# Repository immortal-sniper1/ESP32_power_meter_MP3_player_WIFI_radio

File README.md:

# PCB_test_project_01
 First ESP32 pcb project, it will have power meters( 24V 3A, 5V 0.5A, and self consumption), uSD card, WIFI/BT and the ability to play back MP3/audio file.     
 Also it will feature a power usage meter. It can also be powered from a 18650 Li ion cell, if the USB is alsoo pluged in the cell will start chargeing.
 The chargeing current is limited by the chargeing IC useing a potenciometer as the input. If the red LED is on then the cell is cahrgeing and if the green
 LED is on then the cell is fully charged.
 NOTE: the voltage levels are set by the ICs and it is : 4.2V as charged state and 3V as discharged.
 If the cel voltage reaches 3V or lower then a circuit will activate and disconect the cell from the system so that it will not overdischarge.
 
 V1 is made with ESP32-MINI and that is super hard to hand assemble so V2+ wil use the VROOM

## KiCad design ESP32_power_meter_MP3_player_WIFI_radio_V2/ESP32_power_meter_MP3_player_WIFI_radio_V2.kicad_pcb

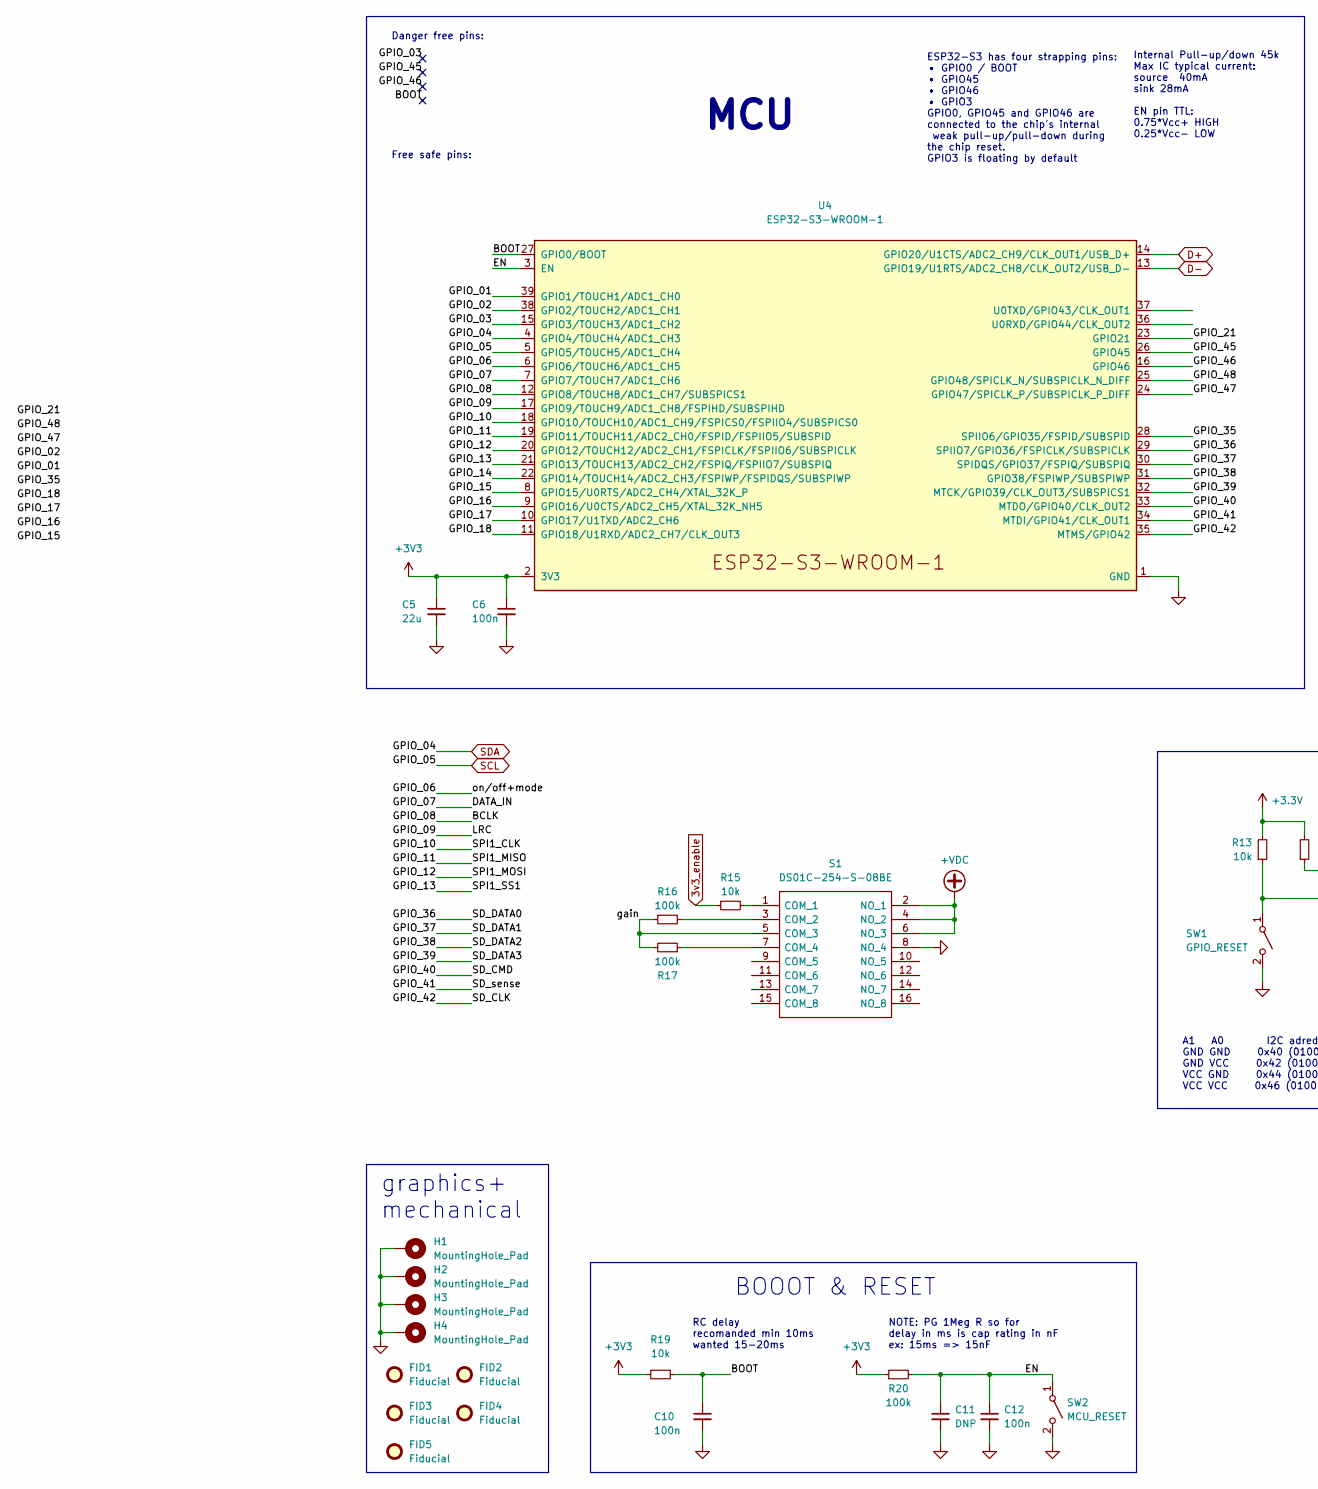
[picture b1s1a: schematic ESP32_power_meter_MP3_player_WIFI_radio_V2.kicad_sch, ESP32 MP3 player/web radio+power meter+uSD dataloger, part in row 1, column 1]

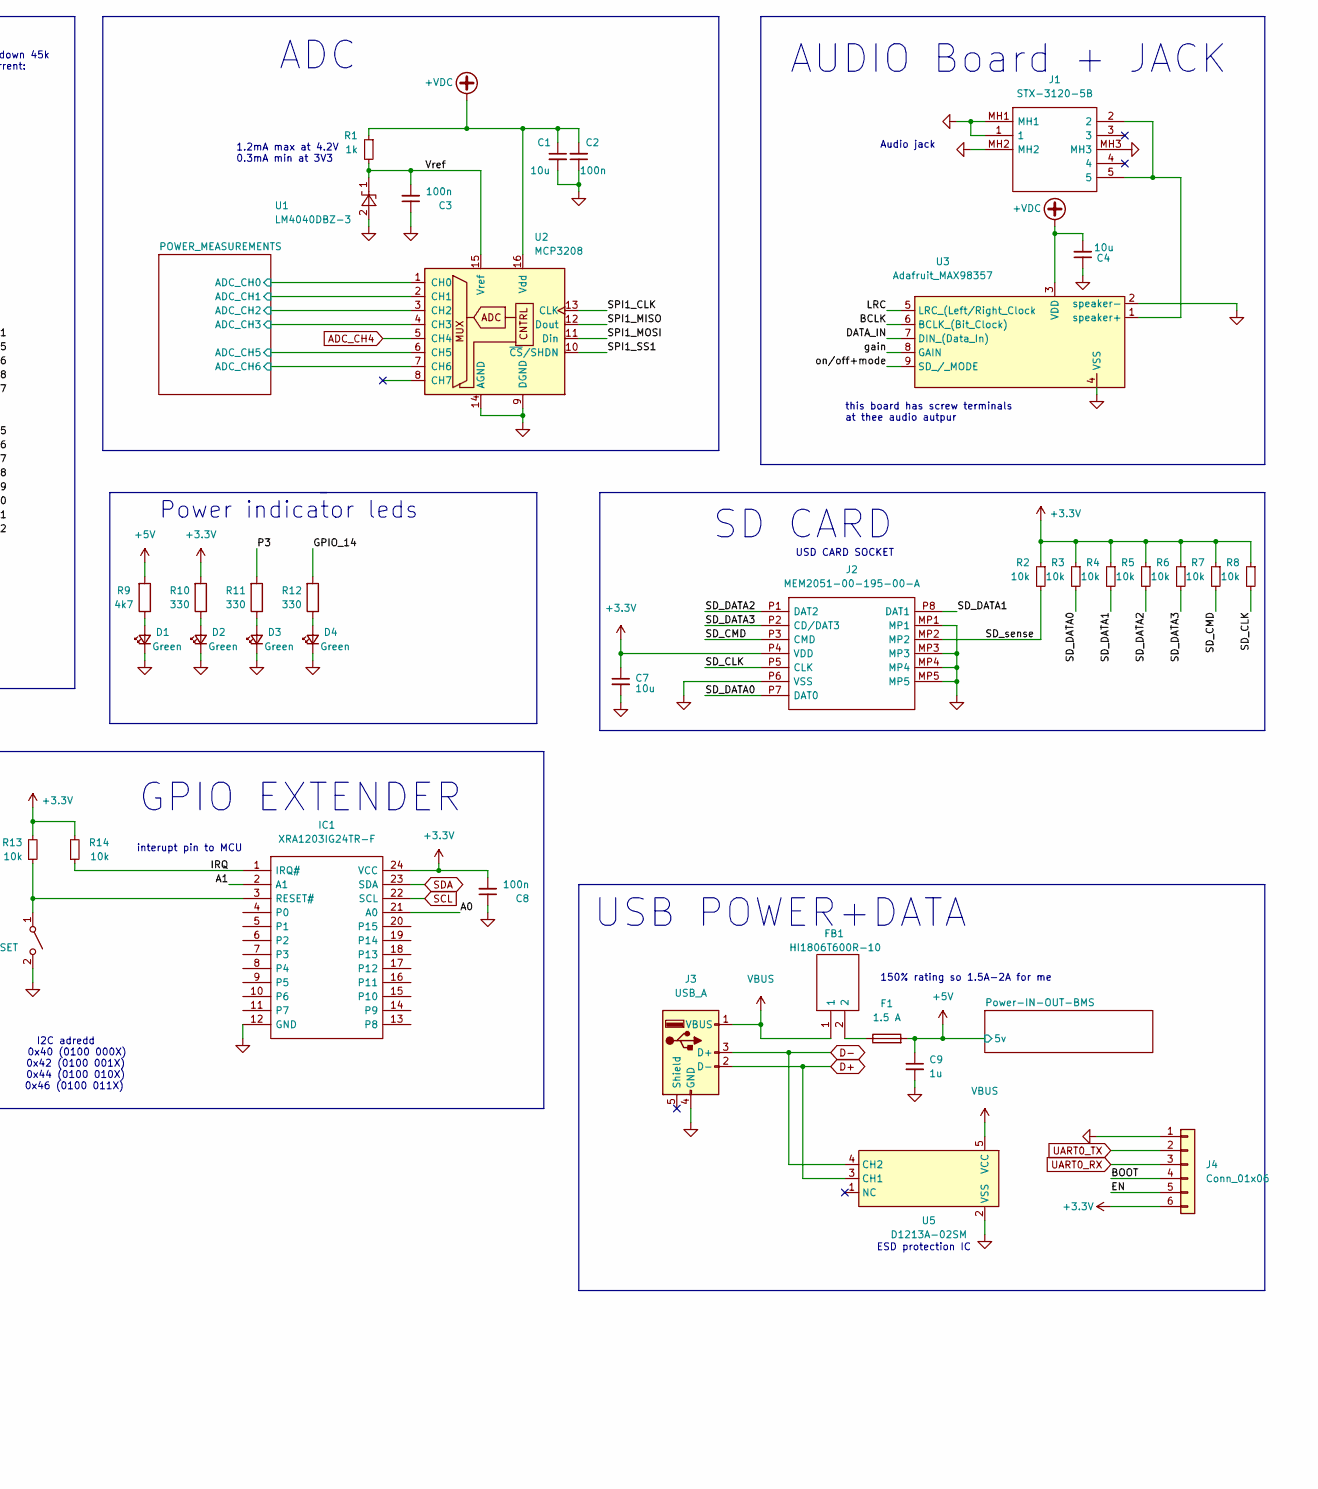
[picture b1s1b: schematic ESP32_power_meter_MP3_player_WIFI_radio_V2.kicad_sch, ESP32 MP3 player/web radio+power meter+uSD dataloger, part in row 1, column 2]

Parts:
C1, C4, C7: 10u; C_0805_2012Metric
C2, C3, C6, C8, C10, C12: 100n; C_0603_1608Metric_Pad1.08x0.95mm_HandSolder
C5: 22u; C_0805_2012Metric_Pad1.18x1.45mm_HandSolder
C9: 1u; C_0603_1608Metric_Pad1.08x0.95mm_HandSolder
C11: DNP; C_0603_1608Metric_Pad1.08x0.95mm_HandSolder
D1, D2, D3, D4: Green; LED_0603_1608Metric_Pad1.05x0.95mm_HandSolder
F1: 1.5 A; Fuse_1812_4532Metric
FB1: HI1806T600R-10; BEADC4516X185N; Mouser Part Number 875-HI1806T600R-10
FID1: Fiducial; Fiducial_0.5mm_Mask1mm
FID2: Fiducial; KiCad-Logo2_6mm_SilkScreen
FID3: Fiducial; Polarity_Center_Positive_6mm_SilkScreen
FID4: Fiducial; WEEE-Logo_5.6x8mm_SilkScreen
FID5: Fiducial; OSHW-Logo_5.7x6mm_SilkScreen
H1, H2, H3, H4: MountingHole_Pad; MountingHole_3.2mm_M3
IC1: XRA1203IG24TR-F; SOP65P640X120-24N; Mouser Part Number 701-XRA1203IG24TR-F
J1: STX-3120-5B; STX31205B; Mouser Part Number 806-STX-3120-5B
J2: MEM2051-00-195-00-A; MEM20510019500A; Mouser Part Number 640-MEM20510019500A
J3: USB_A; USB_A_Molex_67643_Horizontal
J4: Conn_01x06; PinHeader_1x06_P2.54mm_Vertical
R1: 1k; R_0603_1608Metric_Pad0.98x0.95mm_HandSolder
R2, R3, R4, R5, R6, R7, R8, R13, R14, R15, R19: 10k; R_0603_1608Metric_Pad0.98x0.95mm_HandSolder
R9: 4k7; R_0603_1608Metric_Pad0.98x0.95mm_HandSolder
R10, R11, R12: 330; R_0603_1608Metric_Pad0.98x0.95mm_HandSolder
R16, R17, R20: 100k; R_0603_1608Metric_Pad0.98x0.95mm_HandSolder
S1: DS01C-254-S-08BE; DS01C254S08BE; Mouser Part Number 490-DS01C-254-S-08BE
SW1: GPIO_RESET; PTS526SK15SMTR2LFS
SW2: MCU_RESET; PTS526SK15SMTR2LFS
U1: LM4040DBZ-3; SOT-23
U2: MCP3208; SOIC-16_3.9x9.9mm_P1.27mm
U3: Adafruit_MAX98357; Adafruit MAX98357 I2S Class-D Mono
U4: ESP32-S3-WROOM-1
U5: D1213A-02SM; SOT-23-5_HandSoldering

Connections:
3v3_enable: R15.1; also elsewhere on the board
+3.3V: C7.1, C8.2, IC1.24 (VCC), J2.P4 (VDD), J4.6, R2.1, R3.1, R4.1, R5.1, R6.1, R7.1, R8.1, R10.2, R13.2, R14.2; also elsewhere on the board
+3V3: C5.1, C6.1, R19.2, R20.1, U4.2 (3V3); also elsewhere on the board
+5V: C9.1, F1.2, R9.2; also elsewhere on the board
+VDC: C1.1, C2.2, C4.2, R1.1, S1.2 (NO_1), S1.4 (NO_2), S1.6 (NO_3), U2.16 (Vdd), U3.3 (VDD); also elsewhere on the board
/A0: IC1.21 (A0)
/A1: IC1.2 (A1)
/BCLK: U3.6 (BCLK_(Bit_Clock)), U4.12 (GPIO8/TOUCH8/ADC1_CH7/SUBSPICS1)
/BOOT: C10.1, J4.4, R19.1, U4.27 (GPIO0/BOOT)
/DATA_IN: U3.7 (DIN_(Data_In)), U4.7 (GPIO7/TOUCH7/ADC1_CH6)
/EN: C11.1, C12.1, J4.5, R20.2, SW2.1 (A), U4.3 (EN)
/GPIO_01: U4.39 (GPIO1/TOUCH1/ADC1_CH0)
/GPIO_02: U4.38 (GPIO2/TOUCH2/ADC1_CH1)
/GPIO_03: U4.15 (GPIO3/TOUCH3/ADC1_CH2)
/GPIO_06: U3.9 (SD_/_MODE), U4.6 (GPIO6/TOUCH6/ADC1_CH5)
/GPIO_09: U3.5 (LRC_(Left/Right_Clock), U4.17 (GPIO9/TOUCH9/ADC1_CH8/FSPIHD/SUBSPIHD)
/GPIO_10: U2.13 (CLK), U4.18 (GPIO10/TOUCH10/ADC1_CH9/FSPICS0/FSPIIO4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)
/GPIO_11: U2.12 (Dout), U4.19 (GPIO11/TOUCH11/ADC2_CH0/FSPID/FSPIIO5/S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)
/GPIO_12: U2.11 (Din), U4.20 (GPIO12/TOUCH12/ADC2_CH1/FSPICLK/FSPIIO6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)
/GPIO_13: U2.10 (~CS/SHDN), U4.21 (GPIO13/TOUCH13/ADC2_CH2/FSPIQ/FSPIIO7/S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)
/GPIO_14: R12.2, U4.22 (GPIO14/TOUCH14/ADC2_CH3/FSPIWP/FSPIDQS/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)
/GPIO_15: U4.8 (GPIO15/U0RTS/ADC2_CH4/XTAL_32K_P)
/GPIO_16: U4.9 (GPIO16/U0CTS/ADC2_CH5/XTAL_32K_NH5)
/GPIO_17: U4.10 (GPIO17/U1TXD/ADC2_CH6)
/GPIO_18: U4.11 (GPIO18/U1RXD/ADC2_CH7/CLK_OUT3)
/GPIO_21: U4.23 (GPIO21)
/GPIO_35: U4.28 (SPIIO6/GPIO35/FSPID/SUBSPID)
/GPIO_36: J2.P7 (DAT0), R3.2, U4.29 (SPIIO7/GPIO36/FSPICLK/SUBSPICLK)
/GPIO_37: J2.P8 (DAT1), R4.2, U4.30 (SPIDQS/GPIO37/FSPIQ/SUBSPIQ)
/GPIO_38: J2.P1 (DAT2), R5.2, U4.31 (GPIO38/FSPIWP/SUBSPIWP)
/GPIO_39: J2.P2 (CD/DAT3), R6.2, U4.32 (MTCK/GPIO39/CLK_OUT3/SUBSPICS1)
/GPIO_40: J2.P3 (CMD), R7.2, U4.33 (MTDO/GPIO40/CLK_OUT2)
/GPIO_41: J2.MP2, R2.2, U4.34 (MTDI/GPIO41/CLK_OUT1)
/GPIO_42: J2.P5 (CLK), R8.2, U4.35 (MTMS/GPIO42)
/GPIO_45: U4.26 (GPIO45)
/GPIO_46: U4.16 (GPIO46)
/GPIO_47: U4.24 (GPIO47/SPICLK_P/SUBSPICLK_P_DIFF)
/GPIO_48: U4.25 (GPIO48/SPICLK_N/SUBSPICLK_N_DIFF)
/IRQ: IC1.1 (IRQ#), R14.1
/P3: R11.2
/POWER_MEASUREMENTS/ADC_CH0: U2.1 (CH0); also elsewhere on the board
/POWER_MEASUREMENTS/ADC_CH1: U2.2 (CH1); also elsewhere on the board
/POWER_MEASUREMENTS/ADC_CH2: U2.3 (CH2); also elsewhere on the board
/POWER_MEASUREMENTS/ADC_CH3: U2.4 (CH3); also elsewhere on the board
/POWER_MEASUREMENTS/ADC_CH5: U2.6 (CH5); also elsewhere on the board
/POWER_MEASUREMENTS/ADC_CH6: U2.7 (CH6); also elsewhere on the board
/Vref: C3.2, R1.2, U1.1 (K), U2.15 (Vref)
/gain: R16.1, R17.2, S1.5 (COM_3), U3.8 (GAIN)
ADC_CH4: U2.5 (CH4)
D+: J3.2 (D-), U4.14 (GPIO20/U1CTS/ADC2_CH9/CLK_OUT1/USB_D+), U5.3 (CH1)
D-: J3.3 (D+), U4.13 (GPIO19/U1RTS/ADC2_CH8/CLK_OUT2/USB_D-), U5.4 (CH2)
GND: C1.2, C2.1, C3.1, C4.1, C5.2, C6.2, C7.2, C8.1, C9.2, C10.2, C11.2, C12.2, D1.1 (K), D2.1 (K), D3.1 (K), D4.1 (K), H1.1, H2.1, H3.1, H4.1, IC1.12 (GND), J1.1, J1.MH1, J1.MH2, J1.MH3, J2.MP1, J2.MP3, J2.MP4, J2.MP5, J2.P6 (VSS), J3.4 (GND), J4.1, S1.8 (NO_4), SW1.2 (B), SW2.2 (B), U1.2 (A), U2.9 (DGND), U2.14 (AGND), U3.2 (speaker-), U3.4 (VSS), U4.1 (GND), U4.40 (GND), U4.41 (GND), U5.2 (VSS); also elsewhere on the board
unnamed: D1.2 (A), R9.1
unnamed: D2.2 (A), R10.1
unnamed: D3.2 (A), R11.1
unnamed: D4.2 (A), R12.1
unnamed: F1.1, FB1.2
unnamed: IC1.3 (RESET#), R13.1, SW1.1 (A)
unnamed: J1.2, J1.5, U3.1 (speaker+)
unnamed: R15.2, S1.1 (COM_1)
unnamed: R16.2, S1.3 (COM_2)
unnamed: R17.1, S1.7 (COM_4)
SCL: IC1.22 (SCL), U4.5 (GPIO5/TOUCH5/ADC1_CH4)
SDA: IC1.23 (SDA), U4.4 (GPIO4/TOUCH4/ADC1_CH3)
UART0_RX: J4.3
UART0_TX: J4.2
VBUS: FB1.1, J3.1 (VBUS), U5.5 (VCC)

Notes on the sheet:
AUDIO Board + JACK
interupt pin to MCU
USD CARD SOCKET
RC delay recomanded min 10ms wanted 15-20ms
Free safe pins:
Power indicator leds
NOTE: PG 1Meg R so for delay in ms is cap rating in nF ex: 15ms => 15nF
150% rating so 1.5A-2A for me
MCU
ESD protection IC
ESP32-S3 has four strapping pins: • GPIO0 / BOOT • GPIO45 • GPIO46 • GPIO3 GPIO0, GPIO45 and GPIO46 are connected to the chip's internal weak pull-up/pull-down during the chip reset. GPIO3 is floating by default
Internal Pull-up/down 45k Max IC typical current: source 40mA sink 28mA EN pin TTL: 0.75*Vcc+ HIGH 0.25*Vcc- LOW
A1 A0 I2C adredd GND GND 0x40 (0100 000X) GND VCC 0x42 (0100 001X) VCC GND 0x44 (0100 010X) VCC VCC 0x46 (0100 011X)
GPIO EXTENDER
SD CARD
Danger free pins:
USB POWER+DATA
ADC
graphics+ mechanical
1.2mA max at 4.2V 0.3mA min at 3V3
Audio jack
this board has screw terminals at thee audio autpur
BOOOT & RESET

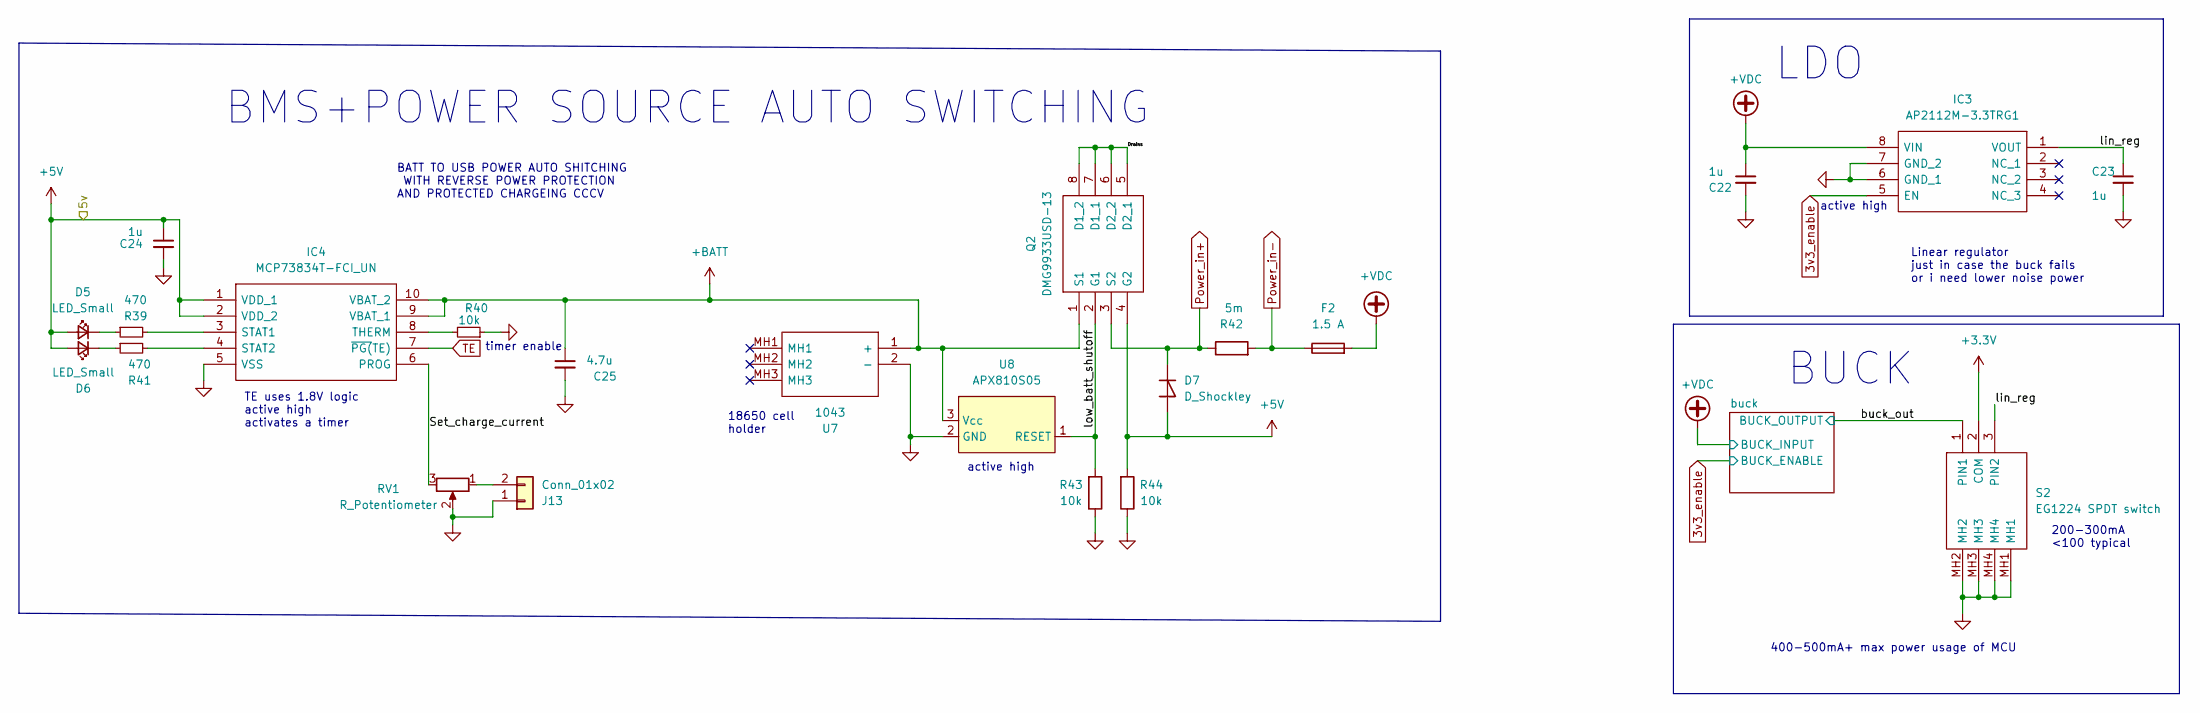
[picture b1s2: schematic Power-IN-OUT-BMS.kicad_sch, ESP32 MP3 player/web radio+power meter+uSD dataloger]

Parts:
C22, C23: 1u; C_0805_2012Metric_Pad1.18x1.45mm_HandSolder
C24: 1u; C_0603_1608Metric_Pad1.08x0.95mm_HandSolder
C25: 4.7u; C_0603_1608Metric_Pad1.08x0.95mm_HandSolder
D5, D6: LED_Small; LED_0603_1608Metric_Pad1.05x0.95mm_HandSolder
D7: D_Shockley; D_DO-15_P5.08mm_Vertical_AnodeUp
F2: 1.5 A; Fuse_1812_4532Metric
IC3: AP2112M-3.3TRG1; SOIC127P600X170-8N; Mouser Part Number 621-AP2112M-3.3TRG1
IC4: MCP73834T-FCI_UN; SOP50P490X110-10N; Mouser Part Number 579-MCP73834T-FCI/UN
J13: Conn_01x02; PinHeader_1x02_P2.54mm_Vertical
Q2: DMG9933USD-13; SOIC127P600X175-8N; Mouser Part Number 621-DMG9933USD-13
R39, R41: 470; R_0603_1608Metric_Pad0.98x0.95mm_HandSolder
R40, R43, R44: 10k; R_0603_1608Metric_Pad0.98x0.95mm_HandSolder
R42: 5m; R_0612_1632Metric_Pad1.18x3.40mm_HandSolder
RV1: R_Potentiometer; Potentiometer_Bourns_3386F_Vertical
S2: EG1224 SPDT switch; EG1224; Mouser Part Number 612-EG1224
U7: 1043; Mouser Part Number 534-1043
U8: APX810S05; SOT-23

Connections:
3v3_enable: IC3.5 (EN); also elsewhere on the board
+3.3V: S2.2 (COM); also elsewhere on the board
+5V: C24.1, D5.2 (A), D6.2 (A), D7.2 (A), IC4.1 (VDD_1), IC4.2 (VDD_2), Q2.4 (G2), R44.2; also elsewhere on the board
+BATT: C25.1, IC4.9 (VBAT_1), IC4.10 (VBAT_2), Q2.1 (S1), U7.1 (+), U8.3 (Vcc)
+VDC: C22.1, F2.2, IC3.8 (VIN); also elsewhere on the board
/Power-IN-OUT-BMS/Drains: Q2.5 (D2_1), Q2.6 (D2_2), Q2.7 (D1_1), Q2.8 (D1_2)
/Power-IN-OUT-BMS/Set_charge_current: IC4.6 (PROG), RV1.3
/Power-IN-OUT-BMS/buck_out: S2.1 (PIN1); also elsewhere on the board
/Power-IN-OUT-BMS/lin_reg: C23.1, IC3.1 (VOUT), S2.3 (PIN2)
/Power-IN-OUT-BMS/low_batt_shutoff: Q2.2 (G1), R43.2, U8.1 (RESET)
GND: C22.2, C23.2, C24.2, C25.2, IC3.6 (GND_1), IC3.7 (GND_2), IC4.5 (VSS), J13.1, R40.1, R43.1, R44.1, RV1.2, S2.MH1, S2.MH2, S2.MH3, S2.MH4, U7.2 (-), U8.2 (GND); also elsewhere on the board
unnamed: D5.1 (K), R39.1
unnamed: D6.1 (K), R41.1
unnamed: IC4.3 (STAT1), R39.2
unnamed: IC4.4 (STAT2), R41.2
unnamed: IC4.8 (THERM), R40.2
unnamed: J13.2, RV1.1
Power_in+: D7.1 (K), Q2.3 (S2), R42.1; also elsewhere on the board
Power_in-: F2.1, R42.2; also elsewhere on the board
TE: IC4.7 (~PG(TE))

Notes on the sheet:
400-500mA+ max power usage of MCU
active high
timer enable
BUCK
TE uses 1.8V logic active high activates a timer
Linear regulator just in case the buck fails or i need lower noise power
BATT TO USB POWER AUTO SHITCHING WITH REVERSE POWER PROTECTION AND PROTECTED CHARGEING CCCV
18650 cell holder
LDO
200-300mA <100 typical
BMS+POWER SOURCE AUTO SWITCHING

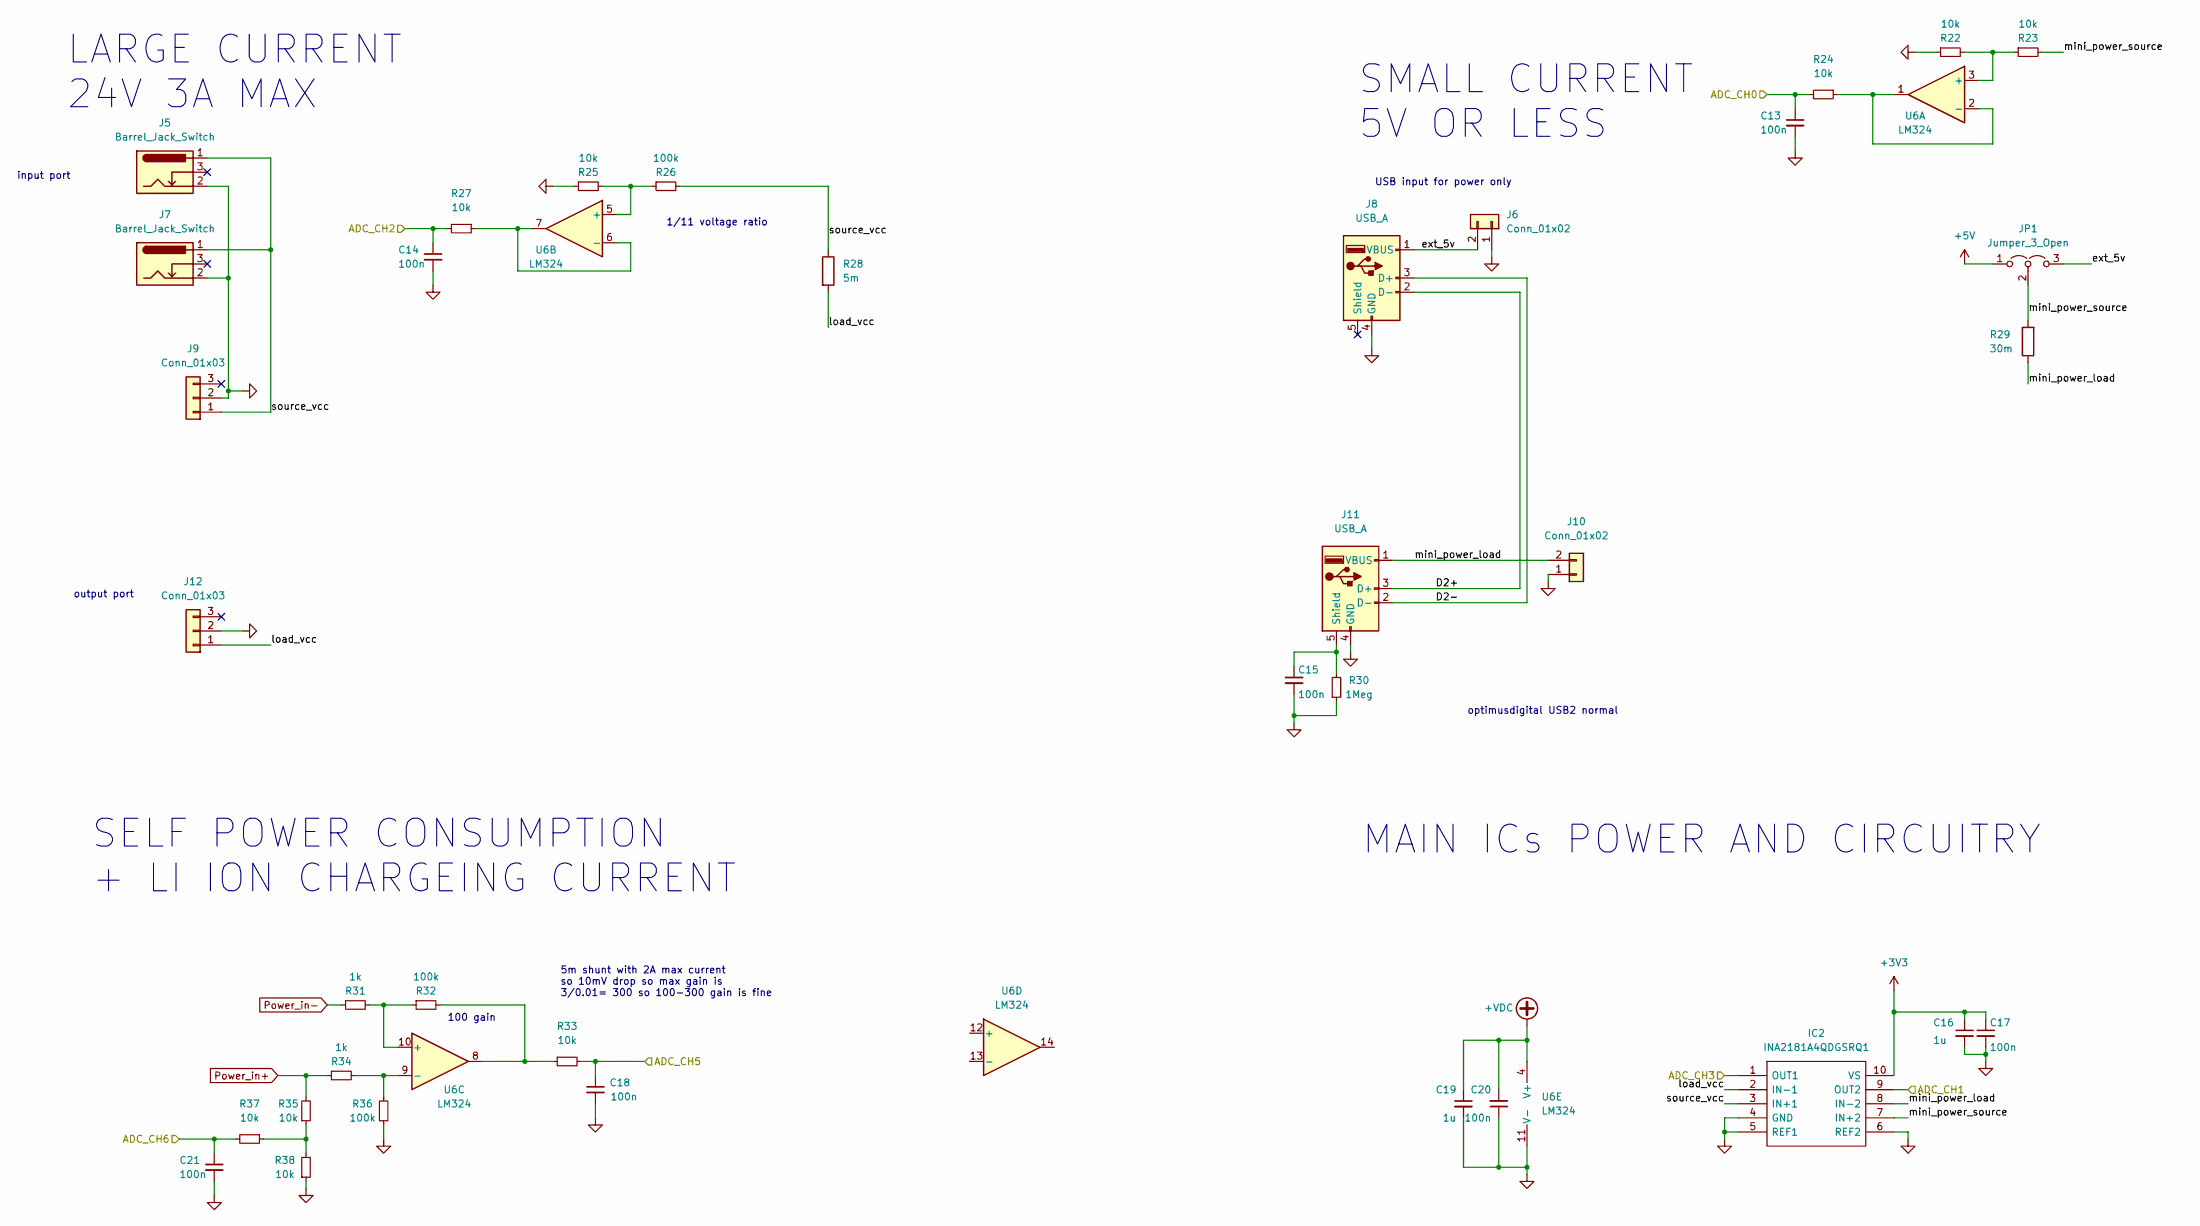
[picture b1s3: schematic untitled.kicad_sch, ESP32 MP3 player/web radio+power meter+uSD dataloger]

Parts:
C13, C14, C15, C17, C18, C20, C21: 100n; C_0603_1608Metric_Pad1.08x0.95mm_HandSolder
C16, C19: 1u; C_0603_1608Metric_Pad1.08x0.95mm_HandSolder
IC2: INA2181A4QDGSRQ1; SOP50P490X110-10N; Mouser Part Number 595-INA2181A4QDGSRQ1
J5: Barrel_Jack_Switch; DC plug jack 5.5-2.5mm
J6, J10: Conn_01x02; TestPoint_2Pads_Pitch5.08mm_Drill1.3mm
J7: Barrel_Jack_Switch; BarrelJack_Wuerth_6941xx301002
J8, J11: USB_A; USB_A_Molex_67643_Horizontal
J9, J12: Conn_01x03; SCREWTERMINAL-5MM-3
JP1: Jumper_3_Open; PinHeader_1x03_P2.54mm_Vertical
R22, R23, R24, R25, R27, R33, R35, R37, R38: 10k; R_0603_1608Metric_Pad0.98x0.95mm_HandSolder
R26, R32, R36: 100k; R_0603_1608Metric_Pad0.98x0.95mm_HandSolder
R28: 5m; R_0612_1632Metric_Pad1.18x3.40mm_HandSolder
R29: 30m; R_0402_1005Metric_Pad0.72x0.64mm_HandSolder
R30: 1Meg; R_0603_1608Metric_Pad0.98x0.95mm_HandSolder
R31, R34: 1k; R_0603_1608Metric_Pad0.98x0.95mm_HandSolder
U6: LM324

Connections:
+3V3: C16.1, C17.1, IC2.10 (VS); also elsewhere on the board
+5V: JP1.1 (A); also elsewhere on the board
+VDC: C19.1, C20.2, U6.4 (V+); also elsewhere on the board
/POWER_MEASUREMENTS/ADC_CH0: C13.1, R24.2; also elsewhere on the board
/POWER_MEASUREMENTS/ADC_CH1: IC2.9 (OUT2); also elsewhere on the board
/POWER_MEASUREMENTS/ADC_CH2: C14.1, R27.2; also elsewhere on the board
/POWER_MEASUREMENTS/ADC_CH3: IC2.1 (OUT1); also elsewhere on the board
/POWER_MEASUREMENTS/ADC_CH5: C18.1, R33.2; also elsewhere on the board
/POWER_MEASUREMENTS/ADC_CH6: C21.1, R37.2; also elsewhere on the board
/POWER_MEASUREMENTS/D2+: J8.2 (D-), J11.3 (D+)
/POWER_MEASUREMENTS/D2-: J8.3 (D+), J11.2 (D-)
/POWER_MEASUREMENTS/ext_5v: J6.2, J8.1 (VBUS), JP1.3 (B)
/POWER_MEASUREMENTS/load_vcc: IC2.2 (IN-1), J12.1, R28.2
/POWER_MEASUREMENTS/mini_power_load: IC2.8 (IN-2), J10.2, J11.1 (VBUS), R29.1
/POWER_MEASUREMENTS/mini_power_source: IC2.7 (IN+2), JP1.2 (C), R23.2, R29.2
/POWER_MEASUREMENTS/source_vcc: IC2.3 (IN+1), J5.1, J7.1, J9.1, R26.2, R28.1
GND: C13.2, C14.2, C15.2, C16.2, C17.2, C18.2, C19.2, C20.1, C21.2, IC2.4 (GND), IC2.5 (REF1), IC2.6 (REF2), J5.2, J6.1, J7.2, J8.4 (GND), J9.2, J10.1, J11.4 (GND), J12.2, R22.1, R25.1, R30.1, R36.1, R38.1, U6.11 (V-); also elsewhere on the board
unnamed: C15.1, J11.5 (Shield), R30.2
unnamed: R22.2, R23.1, U6.3 (+)
unnamed: R24.1, U6.1, U6.2 (-)
unnamed: R25.2, R26.1, U6.5 (+)
unnamed: R27.1, U6.6 (-), U6.7
unnamed: R31.2, R32.1, U6.10 (+)
unnamed: R32.2, R33.1, U6.8
unnamed: R34.2, R36.2, U6.9 (-)
unnamed: R35.1, R37.1, R38.2
Power_in+: R34.1, R35.2; also elsewhere on the board
Power_in-: R31.1; also elsewhere on the board

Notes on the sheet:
USB input for power only
100 gain
SMALL CURRENT 5V OR LESS
1/11 voltage ratio
input port
5m shunt with 2A max current so 10mV drop so max gain is 3/0.01= 300 so 100-300 gain is fine
SELF POWER CONSUMPTION + LI ION CHARGEING CURRENT
output port
LARGE CURRENT 24V 3A MAX
MAIN ICs POWER AND CIRCUITRY
optimusdigital USB2 normal

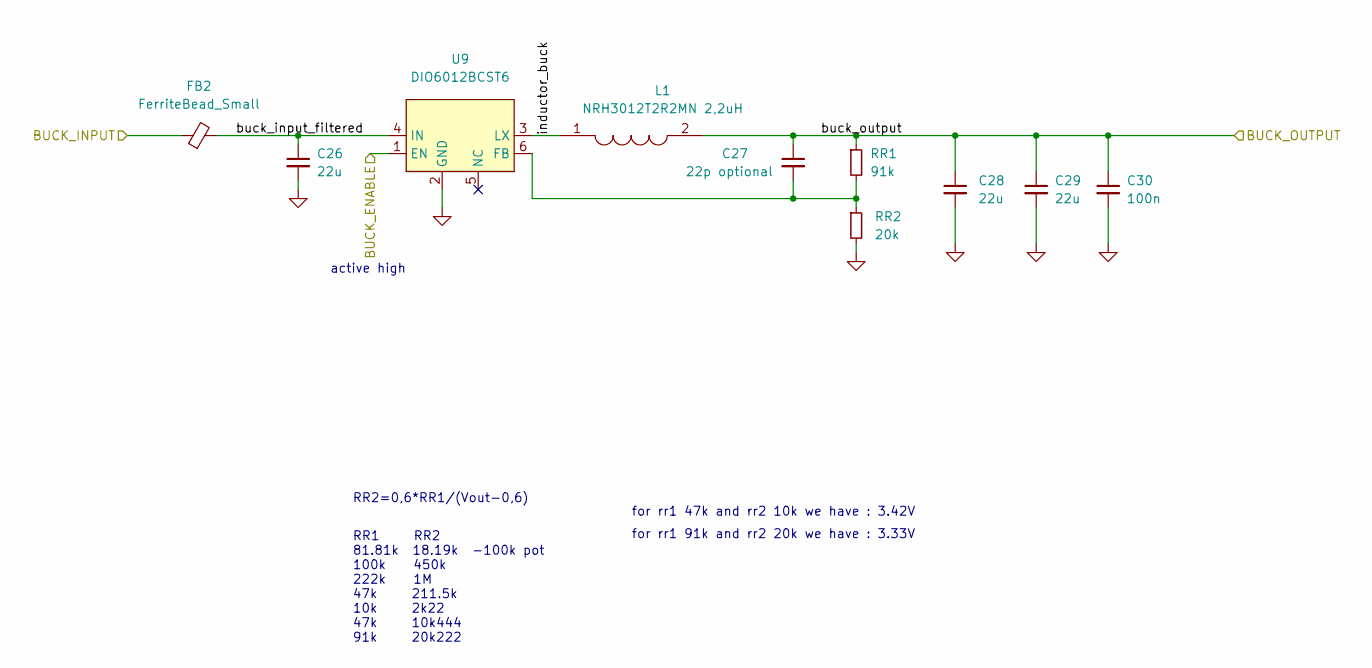
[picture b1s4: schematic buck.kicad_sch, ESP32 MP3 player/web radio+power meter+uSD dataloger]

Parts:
C26, C28, C29: 22u; C_0805_2012Metric
C27: 22p optional; C_0603_1608Metric_Pad1.08x0.95mm_HandSolder
C30: 100n; C_0603_1608Metric
FB2: FerriteBead_Small; R_0603_1608Metric_Pad0.98x0.95mm_HandSolder
L1: NRH3012T2R2MN 2,2uH; NRH3012T220MNV; Mouser Part Number 963-NRH3012T2R2MN
RR1: 91k; R_0805_2012Metric_Pad1.20x1.40mm_HandSolder
RR2: 20k; R_0805_2012Metric_Pad1.20x1.40mm_HandSolder
U9: DIO6012BCST6; SOT-23-6_Handsoldering

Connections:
3v3_enable: U9.1 (EN); also elsewhere on the board
+VDC: FB2.1; also elsewhere on the board
/Power-IN-OUT-BMS/buck/buck_input_filtered: C26.1, FB2.2, U9.4 (IN)
/Power-IN-OUT-BMS/buck/inductor_buck: L1.1, U9.3 (LX)
/Power-IN-OUT-BMS/buck_out: C27.1, C28.1, C29.1, C30.1, L1.2, RR1.1; also elsewhere on the board
GND: C26.2, C28.2, C29.2, C30.2, RR2.2, U9.2 (GND); also elsewhere on the board
unnamed: C27.2, RR1.2, RR2.1, U9.6 (FB)

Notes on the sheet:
for rr1 47k and rr2 10k we have : 3.42V
for rr1 91k and rr2 20k we have : 3.33V
RR2=0,6*RR1/(Vout-0,6)
active high
RR1 RR2 81.81k 18.19k -100k pot 100k 450k 222k 1M 47k 211.5k 10k 2k22 47k 10k444 91k 20k222

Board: 2 copper layers, 128 parts (7 on the bottom side), 81 nets, no tracks yet.

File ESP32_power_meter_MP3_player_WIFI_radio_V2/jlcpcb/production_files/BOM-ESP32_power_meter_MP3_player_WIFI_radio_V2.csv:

Comment,Designator,Footprint,LCSC
100n,"C13,C14,C15,C18,C21,C30",C_0603_1608Metric_Pad1.08x0.95mm_HandSolder,C14663
100n,"C10,C12,C16,C17,C19,C2,C20,C24,C3,C31,C6,C8",C_0603_1608Metric_Pad1.08x0.95mm_HandSolder,C1623
1k,"R1,R31,R34,R39,R41",R_0603_1608Metric_Pad0.98x0.95mm_HandSolder,C21190
LED_Small,D5,LED_0603_1608Metric_Pad1.05x0.95mm_HandSolder,C2286
0,"R49,R50",R_0603_1608Metric_Pad0.98x0.95mm_HandSolder,C22936
330,"R10,R11,R12",R_0603_1608Metric_Pad0.98x0.95mm_HandSolder,C23025
4k7,R9,R_0603_1608Metric_Pad0.98x0.95mm_HandSolder,C23162
91k,RR1,R_0805_2012Metric_Pad1.20x1.40mm_HandSolder,C23265
100k,"R16,R17,R20,R26,R32,R36",R_0603_1608Metric_Pad0.98x0.95mm_HandSolder,C25803
10k,"R13,R14,R15,R18,R19,R2,R21,R22,R23,R24,R25,R27,R3,R33,R35,R37,R38,R4,R40,R43,R44,R45,R46,R48,R5,R51,R6,R7,R8",R_0603_1608Metric,C25804
GPIO_RESET,"SW1,SW2,SW3",PTS526SK15SMTR2LFS,C318884
20k,RR2,R_0805_2012Metric_Pad1.20x1.40mm_HandSolder,C4184
10u,"C1,C22,C23,C25,C26,C28,C29,C4,C5,C7,C9",C_0805_2012Metric,C45783
LM324,U6,SOIC-14_3.9x8.7mm_P1.27mm,C71035
Green,"D1,D2,D3,D4,D6",LED_0603_1608Metric_Pad1.05x0.95mm_HandSolder,C72043
SRV05-4,U5,SOT-23-6,C85364
FerriteBead_Small,FB2,R_0603_1608Metric_Pad0.98x0.95mm_HandSolder,
Conn_01x03,J12,SCREWTERMINAL-5MM-3,
I2C,J16,PinHeader_1x04_P2.54mm_Vertical,
HI1806T600R-10,FB1,BEADC4516X185N,
APX810S05,U8,SOT-23,
LM4040DBZ-3,U1,SOT-23,
Conn_02x10_Odd_Even,J14,PinHeader_2x10_P2.54mm_Vertical,
Conn_01x02,J10,TestPoint_2Pads_Pitch5.08mm_Drill1.3mm,
DIO6012BCST6,U9,SOT-23-6_Handsoldering,
22p optional,C27,C_0603_1608Metric_Pad1.08x0.95mm_HandSolder,
ESP32-S3-WROOM-1,U4,ESP32-S3-WROOM-1,
Conn_01x02,J13,PinHeader_1x02_P2.54mm_Vertical,
Barrel_Jack_Switch,J5,DC plug jack 5.5-2.5mm,
1.5 A,F1,Fuse_1812_4532Metric,
30m,R29,R_0805_2012Metric,
MEM2051-00-195-00-A,J2,MEM20510019500A,
INA2181A4QDGSRQ1,IC2,SOP50P490X110-10N,
DS01C-254-S-08BE,S1,DS01C254S08BE,
DMG9933USD-13,Q2,SOIC127P600X175-8N,
Conn_01x03,J9,SCREWTERMINAL-5MM-3,
Barrel_Jack_Switch,J7,BarrelJack_Wuerth_6941xx301002,
DNP,C11,C_0603_1608Metric_Pad1.08x0.95mm_HandSolder,
XRA1203IG24TR-F,IC1,SOP65P640X120-24N,
USB_A,J11,USB_A_Molex_67643_Horizontal,
1Meg,R30,R_0603_1608Metric_Pad0.98x0.95mm_HandSolder,
L_Small,L2,L_1206_3216Metric,
USB_A,J3,USB_A_Molex_67643_Horizontal,
5m,R42,R_0612_1632Metric_Pad1.18x3.40mm_HandSolder,
Jumper_3_Open,JP1,PinHeader_1x03_P2.54mm_Vertical,
Adafruit_MAX98357,U3,Adafruit MAX98357 I2S Class-D Mono,
EG1224  SPDT switch,S2,EG1224,
"NRH3012T2R2MN  2,2uH",L1,NRH3012T220MNV,
USB_A,J8,USB_A_Molex_67643_Horizontal,
Conn_01x06,J4,PinHeader_1x06_P2.54mm_Vertical,
R_Potentiometer,RV1,Potentiometer_Bourns_3386F_Vertical,
STX-3120-5B,J1,STX31205B,
MCP73834T-FCI_UN,IC4,SOP50P490X110-10N,
MCP3208,U2,SOIC-16_3.9x9.9mm_P1.27mm,
1.5 A,F2,Fuse_1812_4532Metric,
5m,R28,R_0612_1632Metric_Pad1.18x3.40mm_HandSolder,
I2C,J15,PinHeader_1x04_P2.54mm_Vertical,
Conn_01x02,J6,TestPoint_2Pads_Pitch5.08mm_Drill1.3mm,
AP2112M-3.3TRG1,IC3,SOIC127P600X170-8N,
D_Shockley,D7,D_DO-15_P5.08mm_Vertical_AnodeUp,
1043,U7,1043,
